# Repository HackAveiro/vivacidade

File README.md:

Interactive LED wall
====================
This project is being developed to be installed in a public space in Aveiro that was recovered by a wide group of public and citizens entities. [vivacidade.umnovolargo.pt!](http://vivacidade.umnovolargo.pt)  
The interactive wall has 100 LEDs mounted in jam jars ! Each bottle has an RGB LED ( Neopixel ) and LDR sensor for users to physically interact with the wall. The panel is controlled by an Arduino which uses a radio link to communicate with a gateway situated a few hundred meters away and connects the system to the Internet. Because the place has no available electricity or Internet access it's powered by solar panels.  
Users can interact with the system through the Web App: [vivacidade-ledmatrixcontroller!](https://github.com/HackAveiro/vivacidade-ledmatrixcontroller)

Prototype images
===================

GIT Structure
=============

[ADC_BOARD!](ADC_Board)
===========
The system have 10 of this boards to connect all the 100 LED. The ADC board also have ADC chips that convert the LDR light sensors readings. The ADC chips are connected to the Arduino main board via a SPI bus.

PCB Schematic (Left Board)

PCB Layout ( (Left Board)

PCB Schematic (Left Board)

PCB Layout ( (Left Board)

[Gateway_Vivacidade!](Gateway_Vivacidade)
==================
{{Citation needed}} 

[led_board!](led_board)
=========
{{Citation needed}} 

Arduino dependencies
====================
* MCP3008 - https://github.com/nodesign/MCP3008
* RF24 - https://github.com/maniacbug/RF24.git
* FastLED - https://github.com/FastLED/FastLED

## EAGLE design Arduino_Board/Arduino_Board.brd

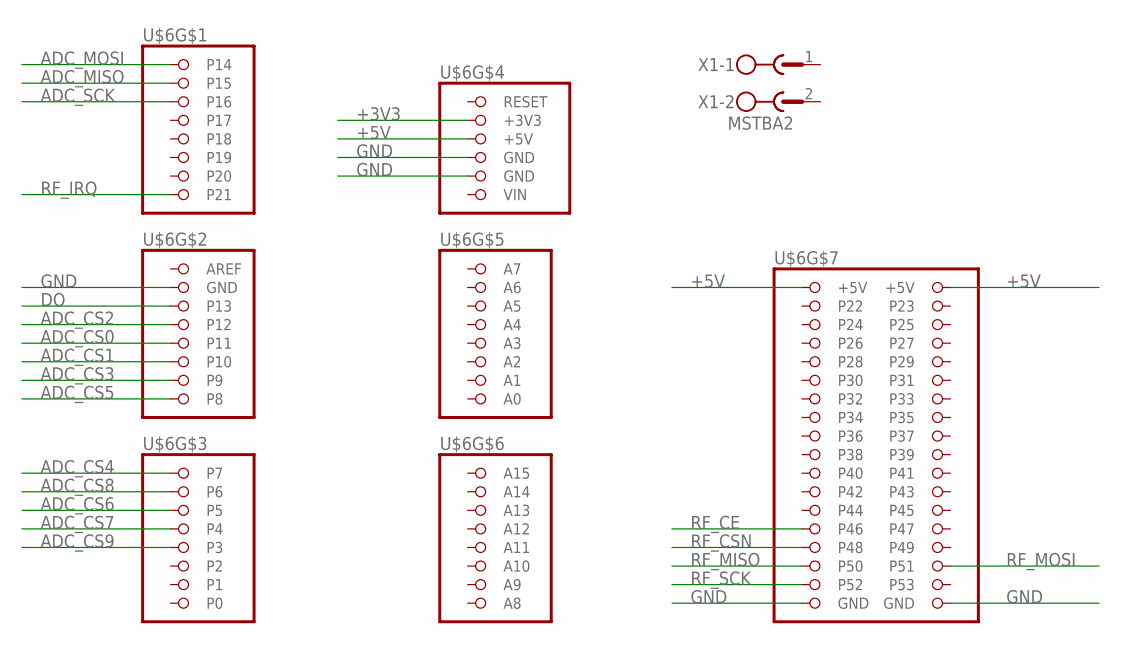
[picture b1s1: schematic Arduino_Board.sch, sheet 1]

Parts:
U$6: ARDUINO_MEGA
X1: MSTBA2

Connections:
+3V3: U$6.+3V3; also elsewhere on the board
+5V: U$6.+5V@1 (+5V), U$6.+5V@2 (+5V), U$6.+5V@3 (+5V); also elsewhere on the board
ADC_CS0: U$6.P11; also elsewhere on the board
ADC_CS1: U$6.P10; also elsewhere on the board
ADC_CS2: U$6.P12; also elsewhere on the board
ADC_CS3: U$6.P9; also elsewhere on the board
ADC_CS4: U$6.P7; also elsewhere on the board
ADC_CS5: U$6.P8; also elsewhere on the board
ADC_CS6: U$6.P5; also elsewhere on the board
ADC_CS7: U$6.P4; also elsewhere on the board
ADC_CS8: U$6.P6; also elsewhere on the board
ADC_CS9: U$6.P3; also elsewhere on the board
ADC_MISO: U$6.P15; also elsewhere on the board
ADC_MOSI: U$6.P14; also elsewhere on the board
ADC_SCK: U$6.P16; also elsewhere on the board
DO: U$6.P13; also elsewhere on the board
GND: U$6.GND@1 (GND), U$6.GND@2 (GND), U$6.GND@3 (GND), U$6.GND@4 (GND), U$6.GND@5 (GND); also elsewhere on the board
RF_CE: U$6.P46; also elsewhere on the board
RF_CSN: U$6.P48; also elsewhere on the board
RF_IRQ: U$6.P21; also elsewhere on the board
RF_MISO: U$6.P50; also elsewhere on the board
RF_MOSI: U$6.P51; also elsewhere on the board
RF_SCK: U$6.P52; also elsewhere on the board

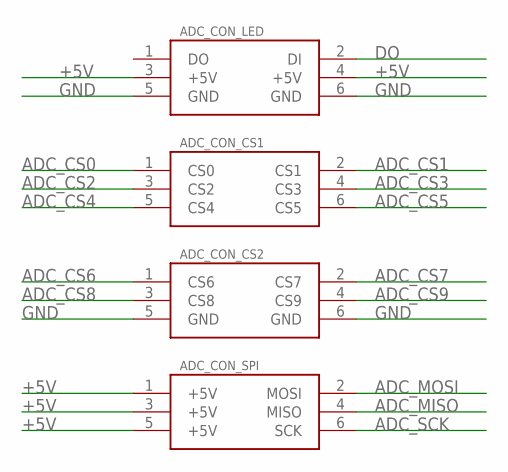
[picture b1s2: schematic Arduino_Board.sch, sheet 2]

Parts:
U$2: ADC_CON_LED; T821_2X03
U$3: ADC_CON_CS1; T821_2X03
U$4: ADC_CON_CS2; T821_2X03
U$5: ADC_CON_SPI; T821_2X03

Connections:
+5V: U$2.3 (+5V), U$2.4 (+5V), U$5.1 (+5V), U$5.3 (+5V), U$5.5 (+5V); also elsewhere on the board
ADC_CS0: U$3.1 (CS0); also elsewhere on the board
ADC_CS1: U$3.2 (CS1); also elsewhere on the board
ADC_CS2: U$3.3 (CS2); also elsewhere on the board
ADC_CS3: U$3.4 (CS3); also elsewhere on the board
ADC_CS4: U$3.5 (CS4); also elsewhere on the board
ADC_CS5: U$3.6 (CS5); also elsewhere on the board
ADC_CS6: U$4.1 (CS6); also elsewhere on the board
ADC_CS7: U$4.2 (CS7); also elsewhere on the board
ADC_CS8: U$4.3 (CS8); also elsewhere on the board
ADC_CS9: U$4.4 (CS9); also elsewhere on the board
ADC_MISO: U$5.4 (MISO); also elsewhere on the board
ADC_MOSI: U$5.2 (MOSI); also elsewhere on the board
ADC_SCK: U$5.6 (SCK); also elsewhere on the board
DO: U$2.2 (DI); also elsewhere on the board
GND: U$2.5 (GND), U$2.6 (GND), U$4.5 (GND), U$4.6 (GND); also elsewhere on the board

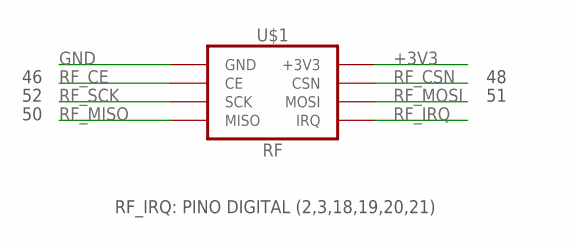
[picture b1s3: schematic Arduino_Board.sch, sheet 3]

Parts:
U$1: RF

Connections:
+3V3: U$1.2 (+3V3); also elsewhere on the board
GND: U$1.1 (GND); also elsewhere on the board
RF_CE: U$1.3 (CE); also elsewhere on the board
RF_CSN: U$1.4 (CSN); also elsewhere on the board
RF_IRQ: U$1.8 (IRQ); also elsewhere on the board
RF_MISO: U$1.7 (MISO); also elsewhere on the board
RF_MOSI: U$1.6 (MOSI); also elsewhere on the board
RF_SCK: U$1.5 (SCK); also elsewhere on the board

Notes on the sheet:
RF_IRQ: PINO DIGITAL (2,3,18,19,20,21)

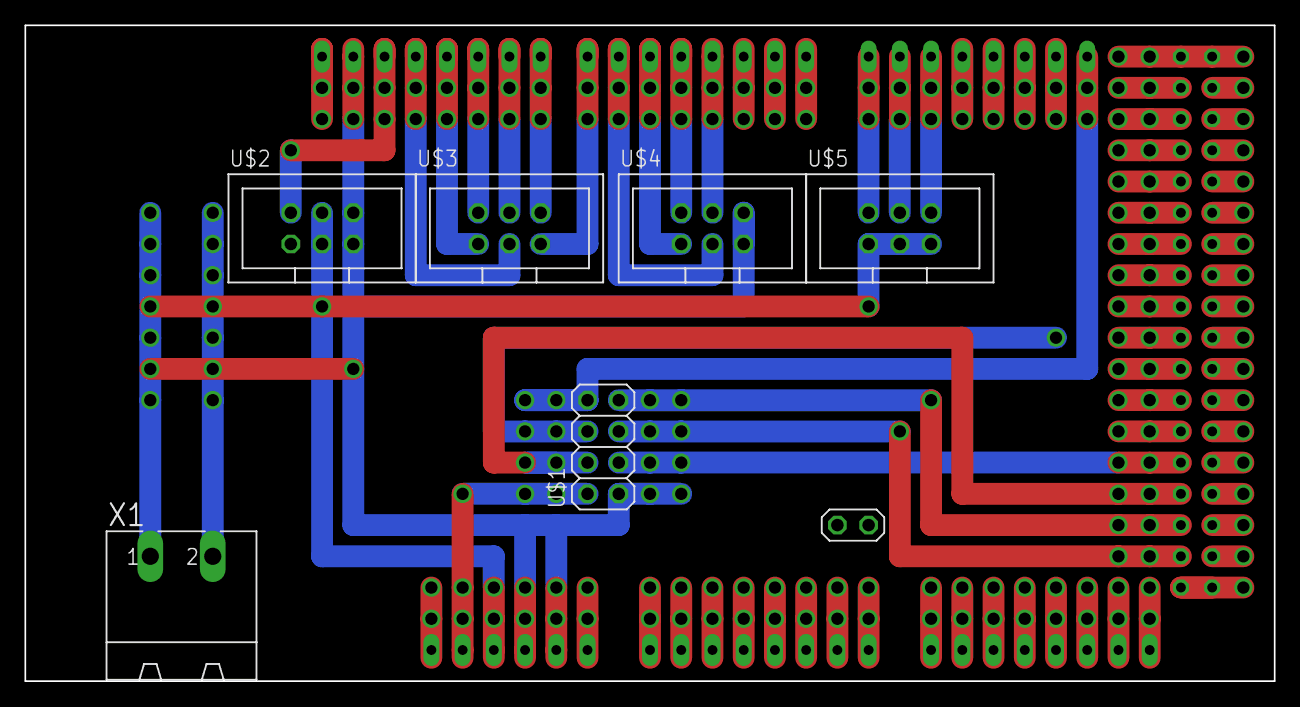
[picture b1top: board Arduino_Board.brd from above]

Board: 2 copper layers, 101.6 x 53.3 mm, 7 parts (0 on the bottom side), 23 nets.

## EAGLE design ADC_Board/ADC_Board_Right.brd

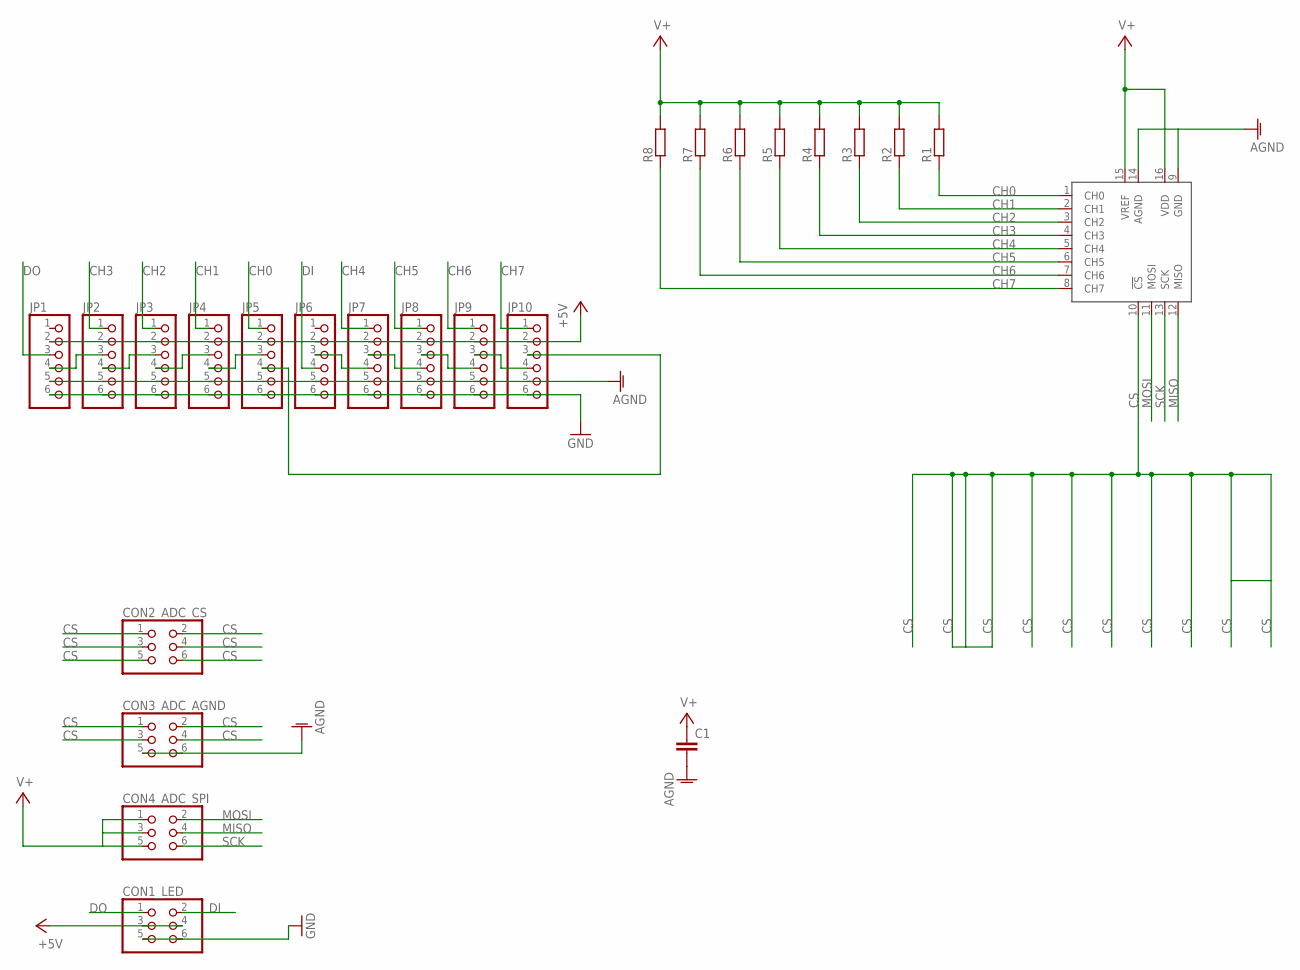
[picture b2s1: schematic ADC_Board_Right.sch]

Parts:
C1: C-EU050-025X075; C050-025X075
CON1_LED, CON2_ADC_CS, CON3_ADC_AGND, CON4_ADC_SPI: PINHD-2X3; 2X03
JP1, JP2, JP3, JP4, JP5, JP6, JP7, JP8, JP9, JP10: PINHD-1X6; 1X06
R1, R2, R3, R4, R5, R6, R7, R8: R-EU_0617_22; 0617/22
U$1: MCP3008P; DIL16

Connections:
+5V: CON1_LED.3, CON1_LED.4, JP1.2, JP2.2, JP3.2, JP4.2, JP5.2, JP6.2, JP7.2, JP8.2, JP9.2, JP10.2
AGND: C1.2, CON3_ADC_AGND.5, CON3_ADC_AGND.6, JP1.5, JP2.5, JP3.5, JP4.5, JP5.5, JP6.5, JP7.5, JP8.5, JP9.5, JP10.5, U$1.9 (GND), U$1.14 (AGND)
CH0: JP5.1, R1.1, U$1.1 (CH0)
CH1: JP4.1, R2.1, U$1.2 (CH1)
CH2: JP3.1, R3.1, U$1.3 (CH2)
CH3: JP2.1, R4.1, U$1.4 (CH3)
CH4: JP7.1, R5.1, U$1.5 (CH4)
CH5: JP8.1, R6.1, U$1.6 (CH5)
CH6: JP9.1, R7.1, U$1.7 (CH6)
CH7: JP10.1, R8.1, U$1.8 (CH7)
CS: CON2_ADC_CS.1, CON2_ADC_CS.2, CON2_ADC_CS.3, CON2_ADC_CS.4, CON2_ADC_CS.5, CON2_ADC_CS.6, CON3_ADC_AGND.1, CON3_ADC_AGND.2, CON3_ADC_AGND.3, CON3_ADC_AGND.4, U$1.10 (!CS)
DI: CON1_LED.2, JP6.4
DO: CON1_LED.1, JP1.3
GND: CON1_LED.5, CON1_LED.6, JP1.6, JP2.6, JP3.6, JP4.6, JP5.6, JP6.6, JP7.6, JP8.6, JP9.6, JP10.6
MISO: CON4_ADC_SPI.4, U$1.12 (MISO)
MOSI: CON4_ADC_SPI.2, U$1.11 (MOSI)
unnamed: JP6.3, JP7.4
unnamed: JP1.4, JP2.3
unnamed: JP2.4, JP3.3
unnamed: JP3.4, JP4.3
unnamed: JP4.4, JP5.3
unnamed: JP5.4, JP10.3
unnamed: JP7.3, JP8.4
unnamed: JP8.3, JP9.4
unnamed: JP9.3, JP10.4
SCK: CON4_ADC_SPI.6, U$1.13 (SCK)
V+: C1.1, CON4_ADC_SPI.1, CON4_ADC_SPI.3, CON4_ADC_SPI.5, R1.2, R2.2, R3.2, R4.2, R5.2, R6.2, R7.2, R8.2, U$1.15 (VREF), U$1.16 (VDD)

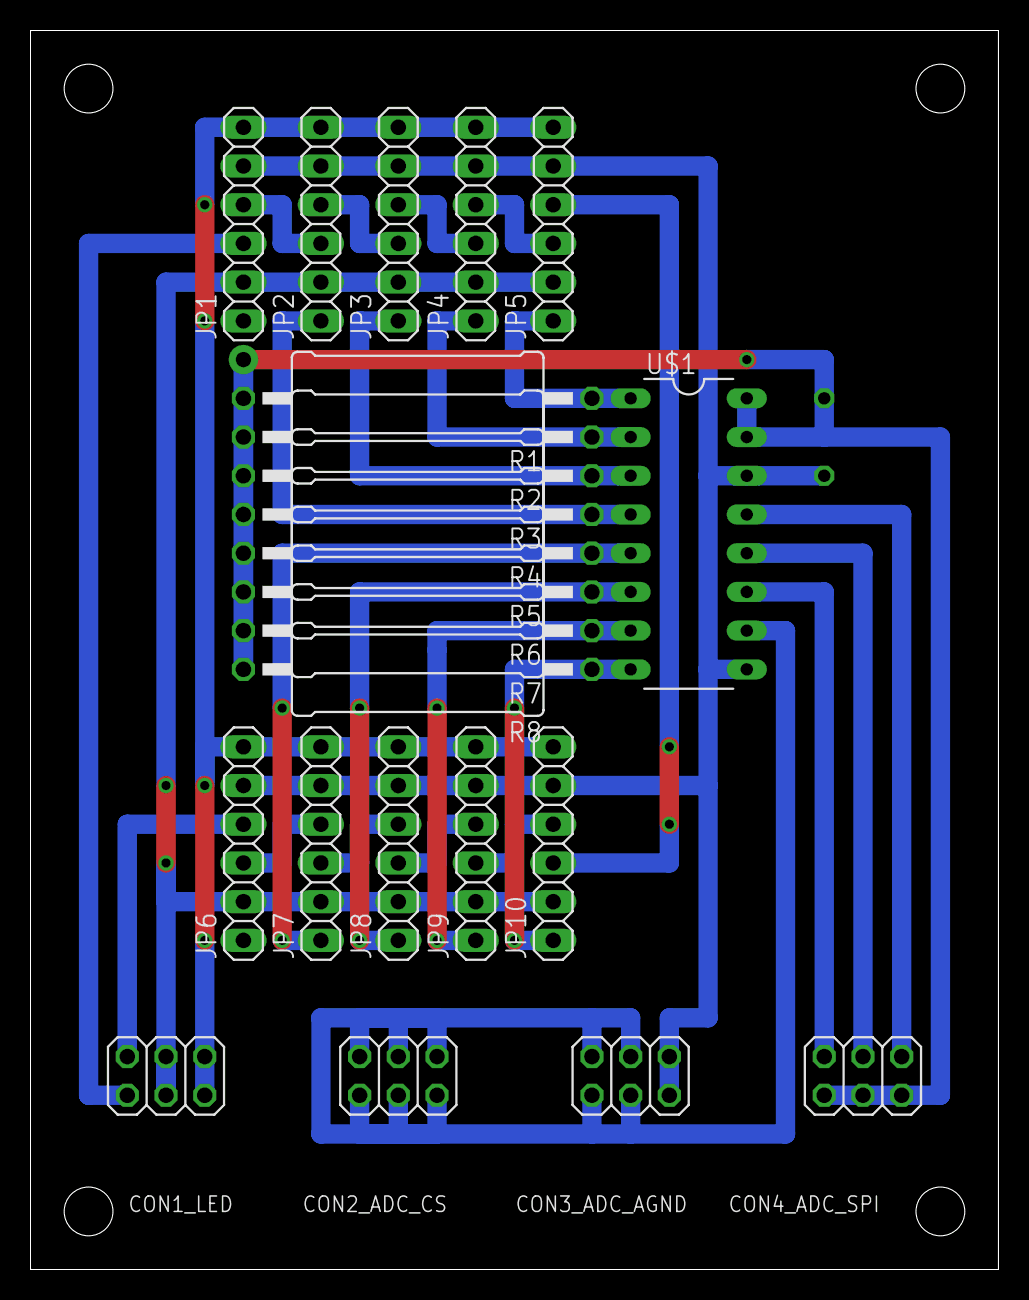
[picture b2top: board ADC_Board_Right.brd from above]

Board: 2 copper layers, 63.5 x 81.3 mm, 24 parts (1 on the bottom side), 27 nets.

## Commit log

2015-06-24 moved
2015-06-24 dependencies
2015-07-08 Teste Matriz de 10 LED
    This code was tested with a 10 LED matrix.
    Protocol: RGB; HEX; ASCII; 6B x 10LED transmited
2015-07-22 added function to convert RGB string to binary 'string'
2015-08-12 changed server + autoack
2015-08-14 fixed sender
2015-08-14 merged receiver
2015-08-16 Complete rewrite
2015-08-19 Imagem
    Imagem criada para a submissão à MakerFaire.
2015-08-19 Adicionada Imagem
    A imagem submetida à candidatura da Maker Faire Lisbon.
2015-08-19 fixed and works
2015-08-27 added mapping function
2015-09-02 Adicionado esquema eléctrico das placas das ADCs
2015-09-02 Alterações ligeiras nos esquemas eléctricos das placas das ADCs.
2015-09-02 Mais formatos de imagens das placas das ADCs
2015-09-02 Led board Kicad source files
2015-09-02 adding led board schematic image file
2015-09-03 Revert "Update README.md"
    This reverts commit 073bfd32e43fffe96677afca54b6772b13c1df0b.
2015-09-03 Cleanup
2015-09-09 Documentação dos pinos de CS das placas das ADCs
2015-09-21 100 LEDs mapped
2015-10-13 Protótipo para uma shield para o arduino mega para ligar as placas "ADC_Board"
2016-03-30 Alterações ligeiras da documentaçao da ADC_Board
2016-03-30 Adicionado ficheiro '.gitignore' a pasta Arduino_Board
2016-03-30 Adicionado programa de teste dos LDRs via ADC_Board
2016-03-30 Adicionado mapa de ligações
